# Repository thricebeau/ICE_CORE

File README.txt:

------------------------------------------------------------------------
README:
This program is the main core of the Integrated Control Environment,
which is a general use process controller that is configured to
interface with numerous types of inputs and outputs ranging from
relays, actuators, temperature sensors, LCD panels, touch screens, etc.

This platform is still under development so it may not work as intended.
------------------------------------------------------------------------

PROJECT TITLE:  	ICE (Integrated Control Environment) Core
PURPOSE OF PROJECT:	This is the core firmware and software of ICE
VERSION or DATE:	Last updated 20120128
HOW TO START:		Load finished code to and Arduino board
AUTHORS:		Beau-James Erion

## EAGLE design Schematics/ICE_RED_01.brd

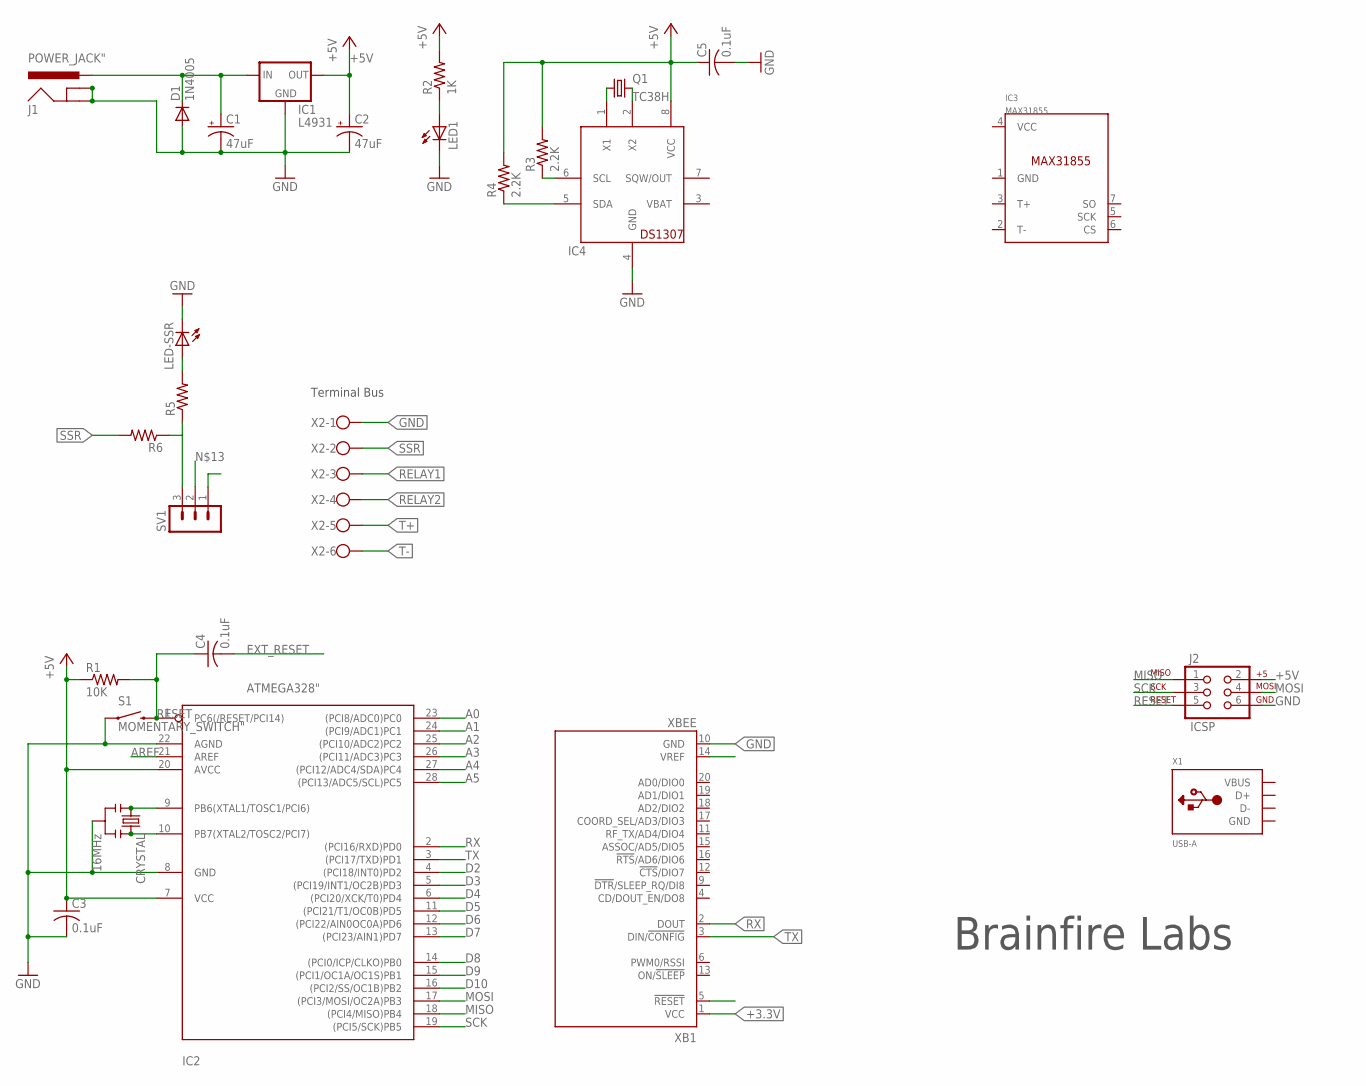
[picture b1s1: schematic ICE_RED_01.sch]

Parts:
C1, C2: 47uF; ELECTROLYTIC_CAP
C3, C4, C5: 0.1uF; UNPOLARIZED_CAP
CRYSTAL: 16MHz; RESONATOR
D1: 1N4005; DO41-10
IC1: L4931; L4931_REGULATOR
IC2: ATMEGA328"; ATMEGA328
IC3: MAX31855; SOIC8
IC4: DS1307; DIL08
J1: POWER_JACK"; POWER_JACK
J2: ICSP; 2X3
LED1: LED3MM; LED
LED-SSR: LED3MM; LED
Q1: TC38H
R1: 10K; RESISTOR
R2: 1K; RESISTOR
R3, R4: 2.2K; 0204/5
R5, R6: RESISTOR1/6WATT; RESISTOR
S1: MOMENTARY_SWITCH"; MOMENTARY_SWITCH
SV1: MA03-1
X1: USB-A; MOLEX_480371000
X2: W237-6
XB1: XBEE

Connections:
+3.3V: XB1.1 (VCC)
+5V: C2.+, C3.1, C5.1, IC1.OUT, IC2.7 (VCC), IC2.20 (AVCC), IC4.8 (VCC), J2.2, R1.1, R2.2, R3.2, R4.2
A0: IC2.23 ((PCI8/ADC0)PC0)
A1: IC2.24 ((PCI9/ADC1)PC1)
A2: IC2.25 ((PCI10/ADC2)PC2)
A3: IC2.26 ((PCI11/ADC3)PC3)
A4: IC2.27 ((PCI12/ADC4/SDA)PC4)
A5: IC2.28 ((PCI13/ADC5/SCL)PC5)
AREF: IC2.21 (AREF)
D2: IC2.4 ((PCI18/INT0)PD2)
D3: IC2.5 ((PCI19/INT1/OC2B)PD3)
D4: IC2.6 ((PCI20/XCK/T0)PD4)
D5: IC2.11 ((PCI21/T1/OC0B)PD5)
D6: IC2.12 ((PCI22/AIN0OC0A)PD6)
D7: IC2.13 ((PCI23/AIN1)PD7)
D8: IC2.14 ((PCI0/ICP/CLKO)PB0)
D9: IC2.15 ((PCI1/OC1A/OC1S)PB1)
D10: IC2.16 ((PCI2/SS/OC1B)PB2)
EXT_RESET: C4.2
GND: C1.-, C2.-, C3.2, C5.2, CRYSTAL.2, D1.A, IC1.GND, IC2.8 (GND), IC2.22 (AGND), IC3.1 (GND), IC4.4 (GND), J1.GND, J1.GNDBREAK, J2.6, LED1.K (C), LED-SSR.K (C), S1.1, X1.4 (GND), X2.1, XB1.10 (GND)
MISO: IC2.18 ((PCI4/MISO)PB4), J2.1
MOSI: IC2.17 ((PCI3/MOSI/OC2A)PB3), J2.4
unnamed: CRYSTAL.1, IC2.9 (PB6(XTAL1/TOSC1/PCI6))
unnamed: C1.+, D1.C, IC1.IN, J1.PWR
unnamed: CRYSTAL.3, IC2.10 (PB7(XTAL2/TOSC2/PCI7))
unnamed: IC4.1 (X1), Q1.1
unnamed: LED1.A, R2.1
unnamed: IC4.2 (X2), Q1.2
unnamed: IC4.5 (SDA), R4.1
unnamed: IC4.6 (SCL), R3.1
unnamed: R5.1, R6.1, SV1.3
unnamed: LED-SSR.A, R5.2
RELAY1: X2.3
RELAY2: X2.4
RESET: C4.1, IC2.1 (PC6(/RESET/PCI14)), J2.5, R1.2, S1.3 (2)
RX: IC2.2 ((PCI16/RXD)PD0), XB1.2 (DOUT)
SCK: IC2.19 ((PCI5/SCK)PB5), J2.3
SSR: R6.2, X2.2
T+: X2.5
T-: X2.6
TX: IC2.3 ((PCI17/TXD)PD1), XB1.3 (DIN/!CONFIG)
VBAT: IC4.3 (VBAT)
VBUS: X1.1 (VBUS)
VCC: IC3.4 (VCC)

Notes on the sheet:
Terminal Bus
Brainfire Labs

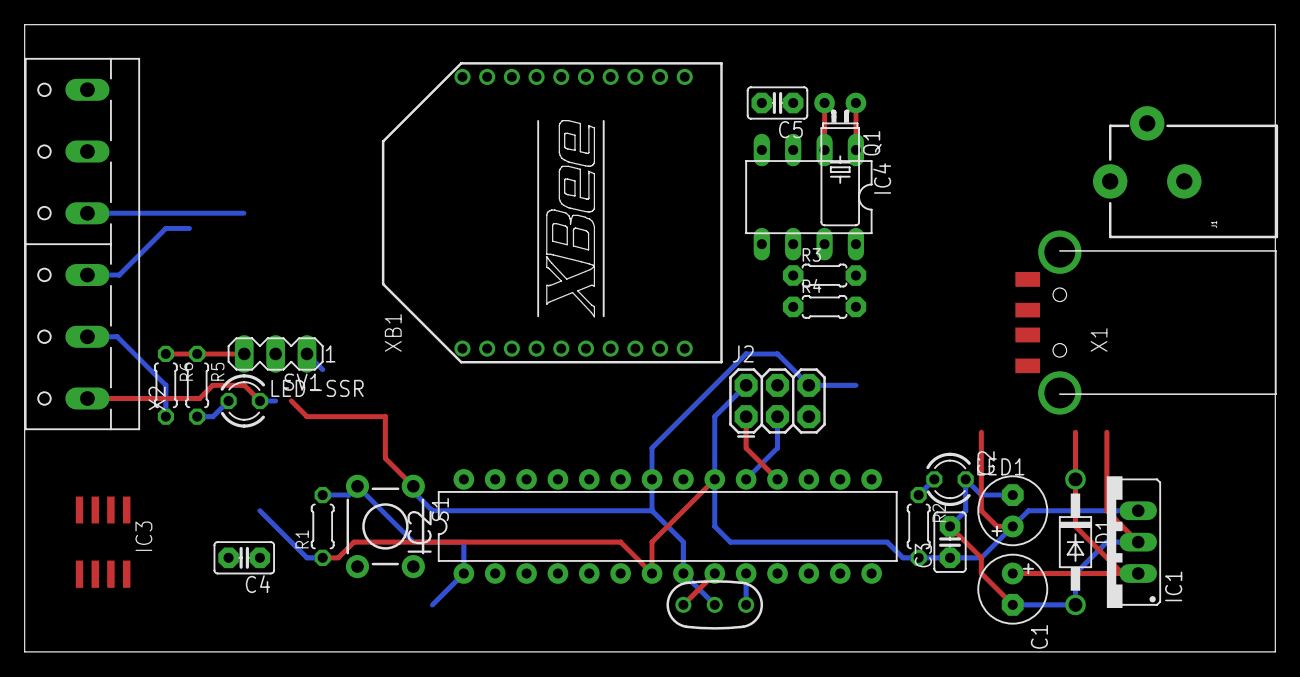
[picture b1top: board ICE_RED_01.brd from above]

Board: 2 copper layers, 101.3 x 50.8 mm, 27 parts (0 on the bottom side), 19 nets.

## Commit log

2013-10-18 Schematics and Firmware Dev
2013-10-18 Relocate old firmware

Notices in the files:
parts and their libraries:
SparkFun-Connectors: Licensing: CC v3.0 Share-Alike You are welcome to use this library for commercial purposes.
